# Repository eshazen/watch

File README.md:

# Smart Watch

See also:  [SOFTWARE.md](SOFTWARE.md)
<br> [BUILD.md](BUILD.md)

Imagining a device similar to a smart watch, but not intended to
connect to a phone and generate alerts.  Instead, I'd like:

* Large, easy-to-read e-ink time display
* Auxiliary info (possibly selected using button):
   * Multiple timezones
   * Alarm/timer time
   * Weather info
   * Any other not-quite realtime info pushed via WiFi

The watch would link to base stations at home and at work for updates.
This could be WiFi (power hungry!), or something like RFM69 (915 MHz).

The idea would be that the watch has WiFi but only powers up every 10min or
so and tries to connect to the last AP, otherwise tries a short list of AP.
Some fairly smart algorithm should recognize when not near an AP and give up,
checking at longer intervals.  A button press should be available to force
WiFi update.

## Rev 1.0

Ordered PCBs and BOM parts (Mouser) on 12/2/22.  

* [schematic](watch-pcb/watch-sch.pdf)

Radio is RFM69HCW (915MHz).  Display is waveshire e-link 1.54 in
(200x200 resolution).  RTC is PCF85263A.
There's an 8-pin (2x4) 2mm "service" connector with pinout:

| Pin | Function |
|-----|----------|
| 1   | 3.3V     |
| 2   | MOSI     |
| 3   | MISO     |
| 4   | SCK      |
| 5   | nRESET   |
| 6   | UART TX  |
| 7   | UART RX  |
| 8   | GND      |

ATMega328 pin assignments:

| Pin | Function | Notes               |
|-----|----------|---------------------|
| PB0 | eRST     | e-ink reset         |
| PB1 | eDC      | e-ink data/control  |
| PB2 | RF_CS    | Radio chip select   |
| PB3 | MOSI     | for radio and e-ink |
| PB4 | MISO     | radio MISO          |
| PB5 | SCK      | for radio and e-ink |
| PB6 | LED1     |                     |
| PB7 | LED2     |                     |
|-----|----------|---------------------|
| PC0 | RF_RST   | Radio reset         |
| PC1 | SW1      | (not installed)     |
| PC2 | SW2      |                     |
| PC3 | RTC_INT  | RTC interrupt       |
| PC4 | RTC_SCL  | RTC I2C clock       |
| PC5 | RTC_SDA  | RTC I2C data        |
| PC6 | nRESET   | MCU reset           |
|-----|----------|---------------------|
| PD0 | RxD      | UART input data     |
| PD1 | TxD      | UART output data    |
| PD2 | SW3      |                     |
| PD3 | SW4      |                     |
| PD5 | DIO0     | Radio DIO0          |
| PD6 | eCS      | e-ink chip select   |
| PD7 | eBUSY    | e-ink busy          |

3D PCB view: 

### Display

Ordered a black/red display from buydisplay.com.  This works ok but has
a ~15s refresh time and doesn't support fast/partial refresh.  My bad!

Ordered another from waveshare which is monochrome and does support
partial refresh.  Holding off on buying anything else until the display
part is working reasonably.

* Waveshare [page](https://www.waveshare.com/product/displays/e-paper/1.54inch-e-paper-module.htm?___SID=U)
[wiki](https://www.waveshare.com/wiki/1.54inch_e-Paper_Module) [data](https://www.waveshare.com/w/upload/e/e5/1.54inch_e-paper_V2_Datasheet.pdf)

This is reasonable, just a bit big.  Another alternative is the waveshare
1.02inch display.

### Radio

Meanwhile, Carlos (of MLRC) suggests BLE or VHF radio as an alternative
to WiFi.  This would require a bit of setup but would be much lower power.

#### VHF/UHF

RFM69 [data](https://cdn.sparkfun.com/datasheets/Wireless/General/RFM69HCW-V1.1.pdf) is 
interesting, but needs a 3 inch antenna.  Possibly it would work
OK if wrapped around the watch band?  These things are cheap ($6.50 for COM-13909 from
Sparkfun).  3.3V.  Needs 16mA to receive, 16..130mA to transmit (depends on settings).
Bit rates are modem-ish up to 156k.  Claims 50m range indoors.
Module is about 0.8" x 0.8" (20.3mm)

nRF24L01 and friends.  2.4GHz.  Bit rate s 250/1M/2M.  Power for Rx:
8.9-13.5mA Power for Tx: 8-11mA.  Fancier protocol with packet
retransmit, etc.  $21 each for WRL-00691.

#### ESP-01

ESP-01 Power Consumption:  
* 170mA working worst case
* 0.9mA "light sleep"
* 10uA "deep sleep"

Datasheet says "...sleep 300s and waking up to connect to the AP
(taking about 0.3~1s), the overall average current is less than 1mA.
Not clear how this is affected if multiple AP must be tried.  Need
to get some ESP-01 and play with them.

So we're looking at ~1mA minimum average power with capability to
deliver ~200mA.  For few days running it would be nice to have
~100mAh.

It seems that on ESP-01 modules you need to wire pin 8 to nRESET so it
can self-wake out of deep sleep.  Otherwise you can just call
ESP.deepSleep(0) and then use the MCU to pulse reset to wake it up.
(see
[note](https://www.tech-spy.co.uk/2019/04/enable-deep-sleep-esp-01/))

## Doco

* Display: [Mfgr page](https://www.buydisplay.com/red-1-54-inch-e-ink-display-module-200x200-for-arduino-raspberry-pi)
* [eInk.md](eInk.md)

## Parts?

* MCU:  ATMega1281-16AUR (64-TQFP)
   * Chosen for it's 8K RAM size so it can hold a 200x200 bitmap for the display
* RTC: 
   * Nisshinbo R2043T-E2-F (2129-R2043T-E2-FCT-ND).  10-VFSOP
   * Nisshinbo R2025S-E2-FE (2129-R2025S-E2-FECT-ND).  14-SOIC
* Thru pin socket
   * Mill-Max 0305-2-15-80-47-27-10-0  (0305-2-15-80-47-27-10-0)
* Side-mount switch
   * Panasonic EVQ-P4MB3K (P15507CT-ND)
* Battery Holder for CR1216
   * Linx BAT-HLD-012-SMT (BAT-HLD-012-SMT-ND)
* or Lipo battery.  There seem to be 100mAh batts 18x14.7mm which are
  cheap ($16/4 on Amazon with a little USB charger thing).  These are
  3.7V so we need a small-ish 3.3V LDO.
* WiFi
   * ESP-01 [data](https://www.microchip.ua/wireless/esp01.pdf)

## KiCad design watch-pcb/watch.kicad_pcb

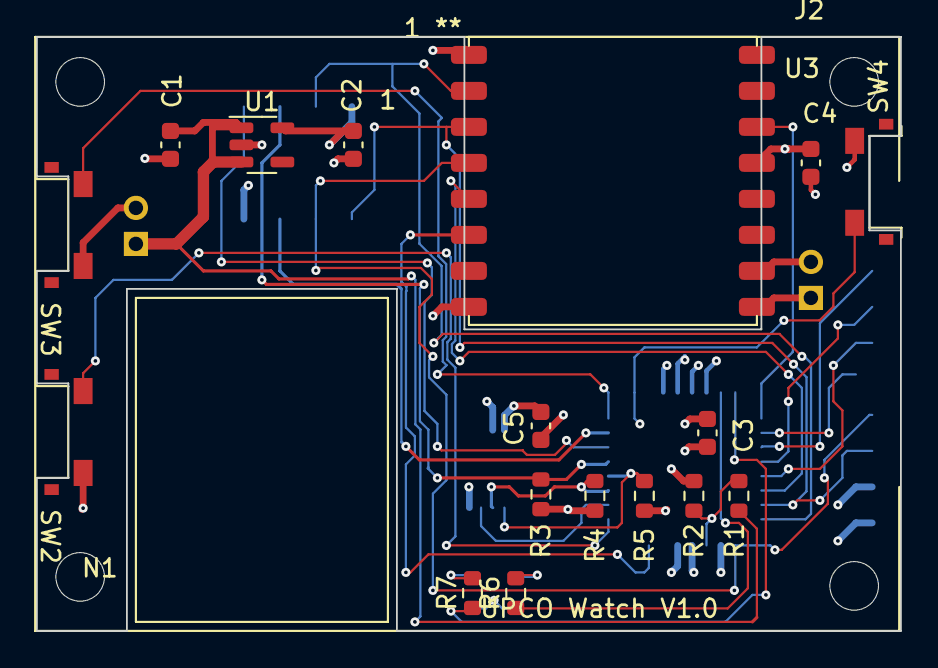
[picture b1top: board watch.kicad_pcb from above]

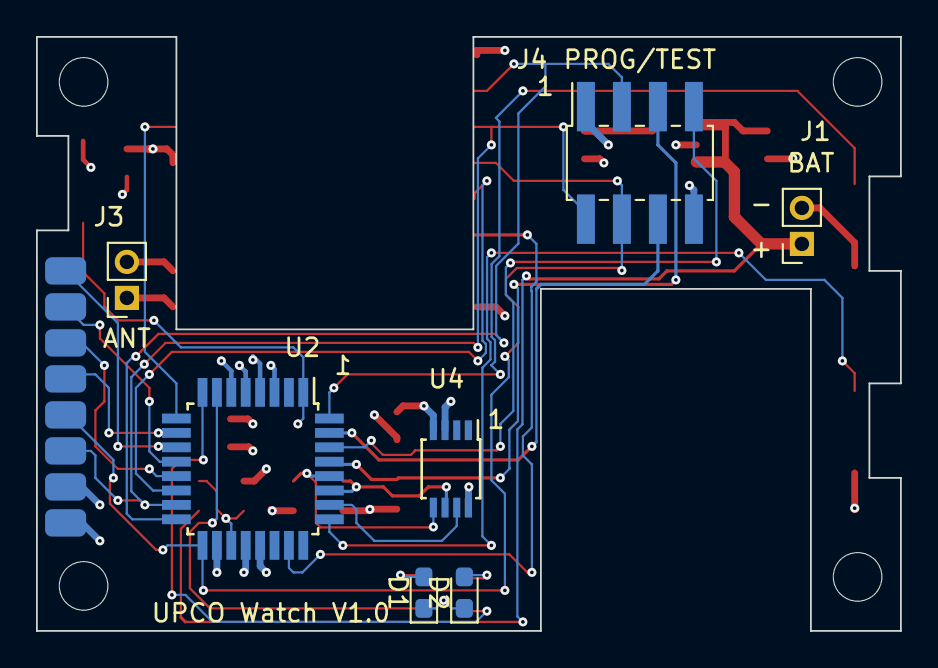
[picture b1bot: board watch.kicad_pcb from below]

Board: 4 copper layers, 48.0 x 33.0 mm, 26 parts (7 on the bottom side), 28 nets.

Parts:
C1, C2: 1uF; C_0603_1608Metric
C3, C4, C5: 0.1uF; C_0603_1608Metric
D1, D2: LED; LED_0603_1608Metric_Pad1.05x0.95mm_HandSolder
J1: Conn_01x02; PinSocket_1x02_P2.00mm_Vertical
J2: Conn_01x08; Waveshare_1.54_no3D
J3: Conn_01x02_Female; PinSocket_1x02_P2.00mm_Vertical
J4: Conn_01x08; PinSocket_2x04_P2.00mm_Vertical_SMD
N1: Battery; LiPo-100mAh
R1, R2, R3: 10k; R_0603_1608Metric
R4, R5: 4.7k; R_0603_1608Metric
R6, R7: 330; R_0603_1608Metric
SW2, SW3, SW4: EVQ-P4MB3K; EVQ-P4
U1: NCP161; SOT-23-5
U2: ATmega328-A; TQFP-32_7x7mm_P0.8mm
U3: RFM69HCW
U4: PCF85263ATT; TSSOP-8_3x3mm_P0.65mm

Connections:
+3.3V: C2.1, C3.1, C4.1, C5.1, J2.8, J4.1, R3.1, R4.1, R5.1, U1.5 (VOUT), U2.4 (VCC), U2.6 (VCC), U2.18 (AVCC), U2.20 (AREF), U3.13 (3.3V), U4.3 (VBAT), U4.8 (VDD)
/LED1: R6.1, U2.7 (XTAL1/PB6)
/LED2: R7.1, U2.8 (XTAL2/PB7)
/MISO: J4.3, U2.16 (PB4), U3.2 (MISO)
/MOSI: J2.6, J4.2, U2.15 (PB3), U3.3 (MOSI)
/RF_CS: U2.14 (PB2), U3.5 (NSS)
/RXD: J4.7, U2.30 (PD0)
/SCK: J2.5, J4.4, U2.17 (PB5), U3.4 (SCK)
/SCL: R4.2, U2.27 (PC4), U4.6 (SCL)
/SDA: R5.2, U2.28 (PC5), U4.5 (SDA)
/TXD: J4.6, U2.31 (PD1)
/eBUSY: J2.1, U2.11 (PD7)
/eCS: J2.4, U2.10 (PD6)
/eDC: J2.3, U2.13 (PB1)
/eRST: J2.2, U2.12 (PB0)
/nRESET: J4.5, R3.2, U2.29 (~RESET/PC6)
GND: C1.2, C2.2, C3.2, C4.2, C5.2, D1.1 (K), D2.1 (K), J1.2, J2.7, J3.2, J4.8, R2.2, SW2.2, SW3.2, SW4.2, U1.2 (GND), U2.3 (GND), U2.5 (GND), U2.21 (GND), U3.1 (GND), U3.8 (GND), U3.10 (GND), U4.4 (VSS)
unnamed: C1.1, J1.1, R1.1, U1.1 (VIN), U1.3 (ON/~OFF)
unnamed: D1.2 (A), R6.2
unnamed: D2.2 (A), R7.2
unnamed: J3.1, U3.9 (ANT)
unnamed: R1.2, R2.1, U2.19 (ADC6)
unnamed: SW2.1, U2.25 (PC2)
unnamed: SW3.1, U2.32 (PD2)
unnamed: SW4.1, U2.1 (PD3)
unnamed: U2.9 (PD5), U3.14 (DIO0)
unnamed: U2.23 (PC0), U3.6 (RESET)
unnamed: U2.26 (PC3), U4.7 (~INTA)

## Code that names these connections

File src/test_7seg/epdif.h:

/**
 *  @filename   :   epdif.h
 *  @brief      :   Header file of epdif.cpp providing EPD interface functions
 *                  Users have to implement all the functions in epdif.cpp
 *  @author     :   Yehui from Waveshare
 *
 *  Copyright (C) Waveshare     August 10 2017
 *
 * Permission is hereby granted, free of charge, to any person obtaining a copy
 * of this software and associated documnetation files (the "Software"), to deal
 * in the Software without restriction, including without limitation the rights
 * to use, copy, modify, merge, publish, distribute, sublicense, and/or sell
 * copies of the Software, and to permit persons to  whom the Software is
 * furished to do so, subject to the following conditions:
 *
 * The above copyright notice and this permission notice shall be included in
 * all copies or substantial portions of the Software.
 *
 * THE SOFTWARE IS PROVIDED "AS IS", WITHOUT WARRANTY OF ANY KIND, EXPRESS OR
 * IMPLIED, INCLUDING BUT NOT LIMITED TO THE WARRANTIES OF MERCHANTABILITY,
 * FITNESS OR A PARTICULAR PURPOSE AND NONINFRINGEMENT. IN NO EVENT SHALL THE
 * AUTHORS OR COPYRIGHT HOLDERS BE LIABLE FOR ANY CLAIM, DAMAGES OR OTHER
 * LIABILITY WHETHER IN AN ACTION OF CONTRACT, TORT OR OTHERWISE, ARISING FROM,
 * OUT OF OR IN CONNECTION WITH THE SOFTWARE OR THE USE OR OTHER DEALINGS IN
 * THE SOFTWARE.
 */

#ifndef EPDIF_H
#define EPDIF_H

#ifdef BAREMETAL
#include <avr/io.h>
#include <stdlib.h>
#include <util/delay.h>
#else
#include <Aruino.h>
#endif

#ifdef BAREMETAL

// define a few things to provide similarity to Arduino world
#define HIGH 1
#define LOW 0

// RST_PIN  PB0
// DC_PIN   PB1
// CS_PIN   PD6
// BUSY_PIN PD7

#define RST_PIN_PORT PORTB
#define RST_PIN_BIT 0
#define RST_PIN_DDR DDRB

#define DC_PIN_PORT PORTB
#define DC_PIN_BIT 1
#define DC_PIN_DDR DDRB

#define CS_PIN_PORT PORTD
#define CS_PIN_BIT 6
#define CS_PIN_DDR DDRD

#define BUSY_PIN_PORT PORTD
#define BUSY_PIN_BIT 7
#define BUSY_PIN_DDR DDRD
#define BUSY_PIN_PIN PIND

// bogus pin numbers used as index into the portz[] struct array below
#define RST_PIN         0
#define DC_PIN          1
#define CS_PIN          2
#define BUSY_PIN        3

// define a struct so we can read/write by pin number
typedef struct {
  volatile uint8_t* port;
  volatile uint8_t* pin;
  uint8_t mask;
} a_port;

static a_port portz[] = {
  &RST_PIN_PORT, NULL, _BV(RST_PIN_BIT),
  &DC_PIN_PORT, NULL, _BV(DC_PIN_BIT),
  &CS_PIN_PORT, NULL, _BV(CS_PIN_BIT),
  &BUSY_PIN_PORT, &BUSY_PIN_PIN, _BV(BUSY_PIN_BIT)
};

#else

//---------- Arduino version ----------

// Pin definition
#define RST_PIN         8
#define DC_PIN          9
#define CS_PIN          10
#define BUSY_PIN        7
#endif

class EpdIf {
public:
    EpdIf(void);
    ~EpdIf(void);

    static int  IfInit(void);
    static void DigitalWrite(int pin, int value); 
    static int  DigitalRead(int pin);
    static void DelayMs(unsigned int delaytime);
    static void SpiTransfer(unsigned char data);
};

#endif

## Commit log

2022-10-18 starting 3D model
2022-10-19 README
2022-10-19 working on 3D model
2022-10-22 starting schematic
2022-10-23 stuff for buydisplays ER-EPM0154 display
2022-10-25 starting test software for waveshare display
2022-10-25 3D work
2022-11-01 working on 3D
2022-11-03 working on PCB
2022-11-03 working on layout
2022-11-04 layout in progress
2022-11-06 working on model
2022-11-08 Update 3D
2022-12-03 as built PCB rev 1.0
2025-05-13 fix readme
2025-05-15 working on analog clock sw
2025-05-15 starting on display list
2025-05-15 working on emulator
2025-05-20 readmes
2025-05-30 blinky firmware
2025-06-02 small updates
2025-06-03 working on uart debug
2025-06-03 candidate I2C debug code
2025-06-04 tweak software, schem notes
2025-06-05 working on the display
2025-06-05 e-ink working!
2025-06-12 debugging display list stuff
2025-06-12 debugging line drawing
